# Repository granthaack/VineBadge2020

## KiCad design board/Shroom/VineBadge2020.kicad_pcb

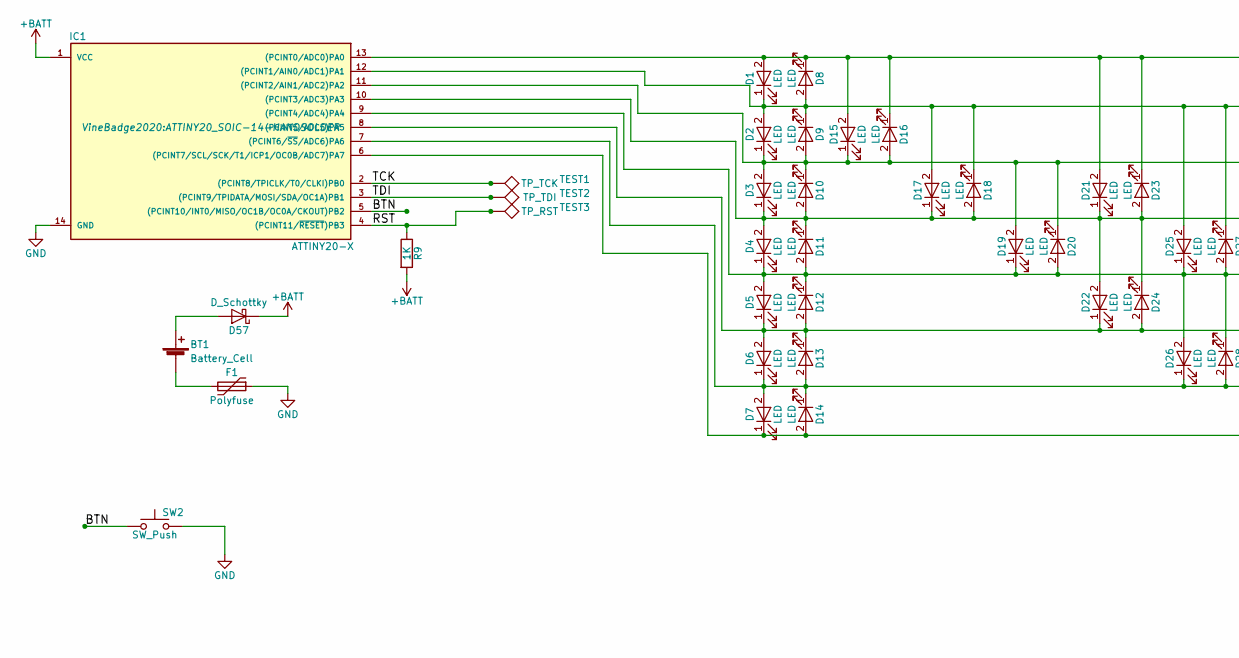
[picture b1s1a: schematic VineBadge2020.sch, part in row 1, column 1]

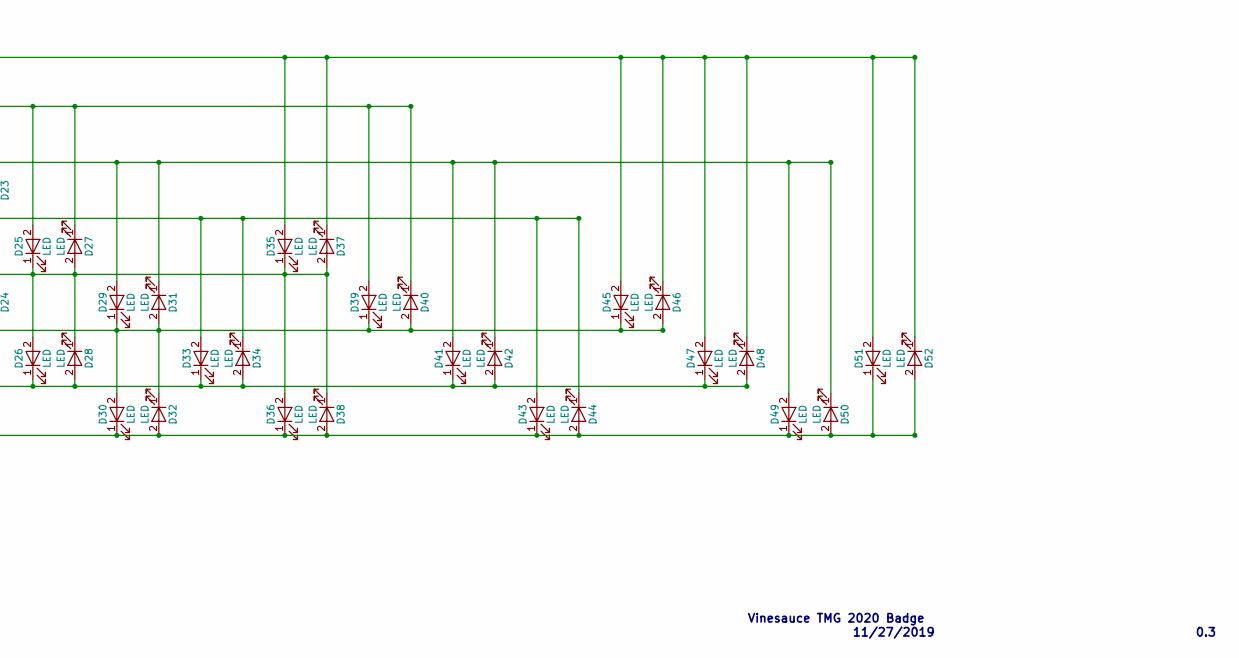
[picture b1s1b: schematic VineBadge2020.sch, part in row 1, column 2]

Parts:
BT1: Battery_Cell; COINCELL_20MM_HANDSOLDER
D1: LED; LED_0603; LCSC C205443
D2, D3, D4, D5, D6, D7, D8, D9, D10, D11, D12, D13, D14, D15, D16, D17, D18, D19, D20, D21, D22, D23, D24, D25, D26, D27, D28, D29, D30, D31, D32, D33, D34, D35, D36, D37, D38, D39, D40, D41, D42, D43, D44, D45, D46, D47, D48, D49, D50, D51, D52: LED; LED_0603
D57: D_Schottky; SOD-323_HandSoldering
F1: Polyfuse; R_0603_HandSoldering
IC1: ATTINY20-X; ATTINY20_SOIC-14-HANDSOLDER
R9: 1K; R_0805_HandSoldering
SW2: SW_Push; SW_SPST_TL3342
TEST1: TP_TCK; TestPoint_Pad_2.5x2.5mm
TEST2: TP_TDI; TestPoint_Pad_2.5x2.5mm
TEST3: TP_RST; TestPoint_Pad_2.5x2.5mm

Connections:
+BATT: D57.1 (K), IC1.1 (VCC), R9.2
/BTN: IC1.5 ((PCINT10/INT0/MISO/OC1B/OC0A/CKOUT)PB2), SW2.1
/RST: IC1.4 ((PCINT11/~RESET~)PB3), R9.1, TEST3.1
/TCK: IC1.2 ((PCINT8/TPICLK/T0/CLKI)PB0), TEST1.1
/TDI: IC1.3 ((PCINT9/TPIDATA/MOSI/SDA/OC1A)PB1), TEST2.1
GND: F1.1, IC1.14 (GND), SW2.2
unnamed: BT1.1 (+), D57.2 (A)
unnamed: BT1.2 (-), F1.2
unnamed: D1.1 (K), D2.2 (A), D8.2 (A), D9.1 (K), D17.2 (A), D18.1 (K), D25.2 (A), D27.1 (K), D39.2 (A), D40.1 (K), IC1.12 ((PCINT1/AIN0/ADC1)PA1)
unnamed: D1.2 (A), D8.1 (K), D15.2 (A), D16.1 (K), D21.2 (A), D23.1 (K), D35.2 (A), D37.1 (K), D45.2 (A), D46.1 (K), D47.2 (A), D48.1 (K), D51.2 (A), D52.1 (K), IC1.13 ((PCINT0/ADC0)PA0)
unnamed: D2.1 (K), D3.2 (A), D9.2 (A), D10.1 (K), D15.1 (K), D16.2 (A), D19.2 (A), D20.1 (K), D29.2 (A), D31.1 (K), D41.2 (A), D42.1 (K), D49.2 (A), D50.1 (K), IC1.11 ((PCINT2/AIN1/ADC2)PA2)
unnamed: D3.1 (K), D4.2 (A), D10.2 (A), D11.1 (K), D17.1 (K), D18.2 (A), D21.1 (K), D22.2 (A), D23.2 (A), D24.1 (K), D33.2 (A), D34.1 (K), D43.2 (A), D44.1 (K), IC1.10 ((PCINT3/ADC3)PA3)
unnamed: D4.1 (K), D5.2 (A), D11.2 (A), D12.1 (K), D19.1 (K), D20.2 (A), D25.1 (K), D26.2 (A), D27.2 (A), D28.1 (K), D35.1 (K), D36.2 (A), D37.2 (A), D38.1 (K), IC1.9 ((PCINT4/ADC4)PA4)
unnamed: D5.1 (K), D6.2 (A), D12.2 (A), D13.1 (K), D22.1 (K), D24.2 (A), D29.1 (K), D30.2 (A), D31.2 (A), D32.1 (K), D39.1 (K), D40.2 (A), D45.1 (K), D46.2 (A), IC1.8 ((PCINT5/ADC5)PA5)
unnamed: D6.1 (K), D7.2 (A), D13.2 (A), D14.1 (K), D26.1 (K), D28.2 (A), D33.1 (K), D34.2 (A), D41.1 (K), D42.2 (A), D47.1 (K), D48.2 (A), IC1.7 ((PCINT6/~SS~/ADC6)PA6)
unnamed: D7.1 (K), D14.2 (A), D30.1 (K), D32.2 (A), D36.1 (K), D38.2 (A), D43.1 (K), D44.2 (A), D49.1 (K), D50.2 (A), D51.1 (K), D52.2 (A), IC1.6 ((PCINT7/SCL/SCK/T1/ICP1/OC0B/ADC7)PA7)

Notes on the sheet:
Vinesauce TMG 2020 Badge
11/27/2019
0.3

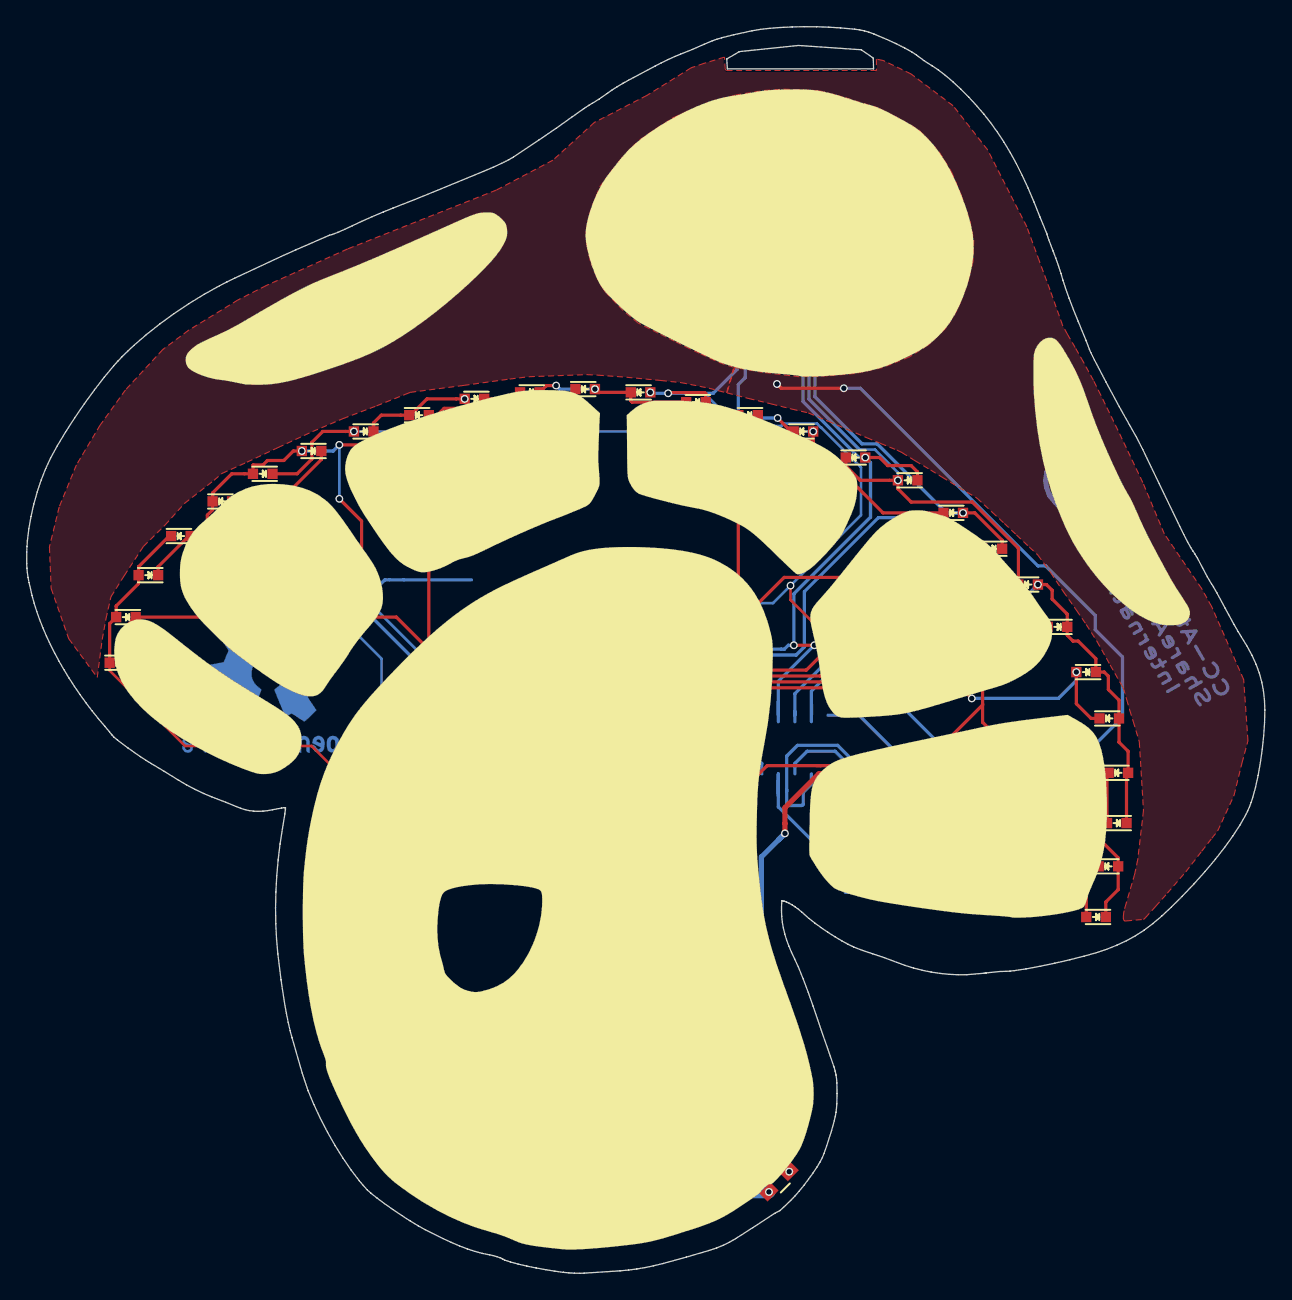
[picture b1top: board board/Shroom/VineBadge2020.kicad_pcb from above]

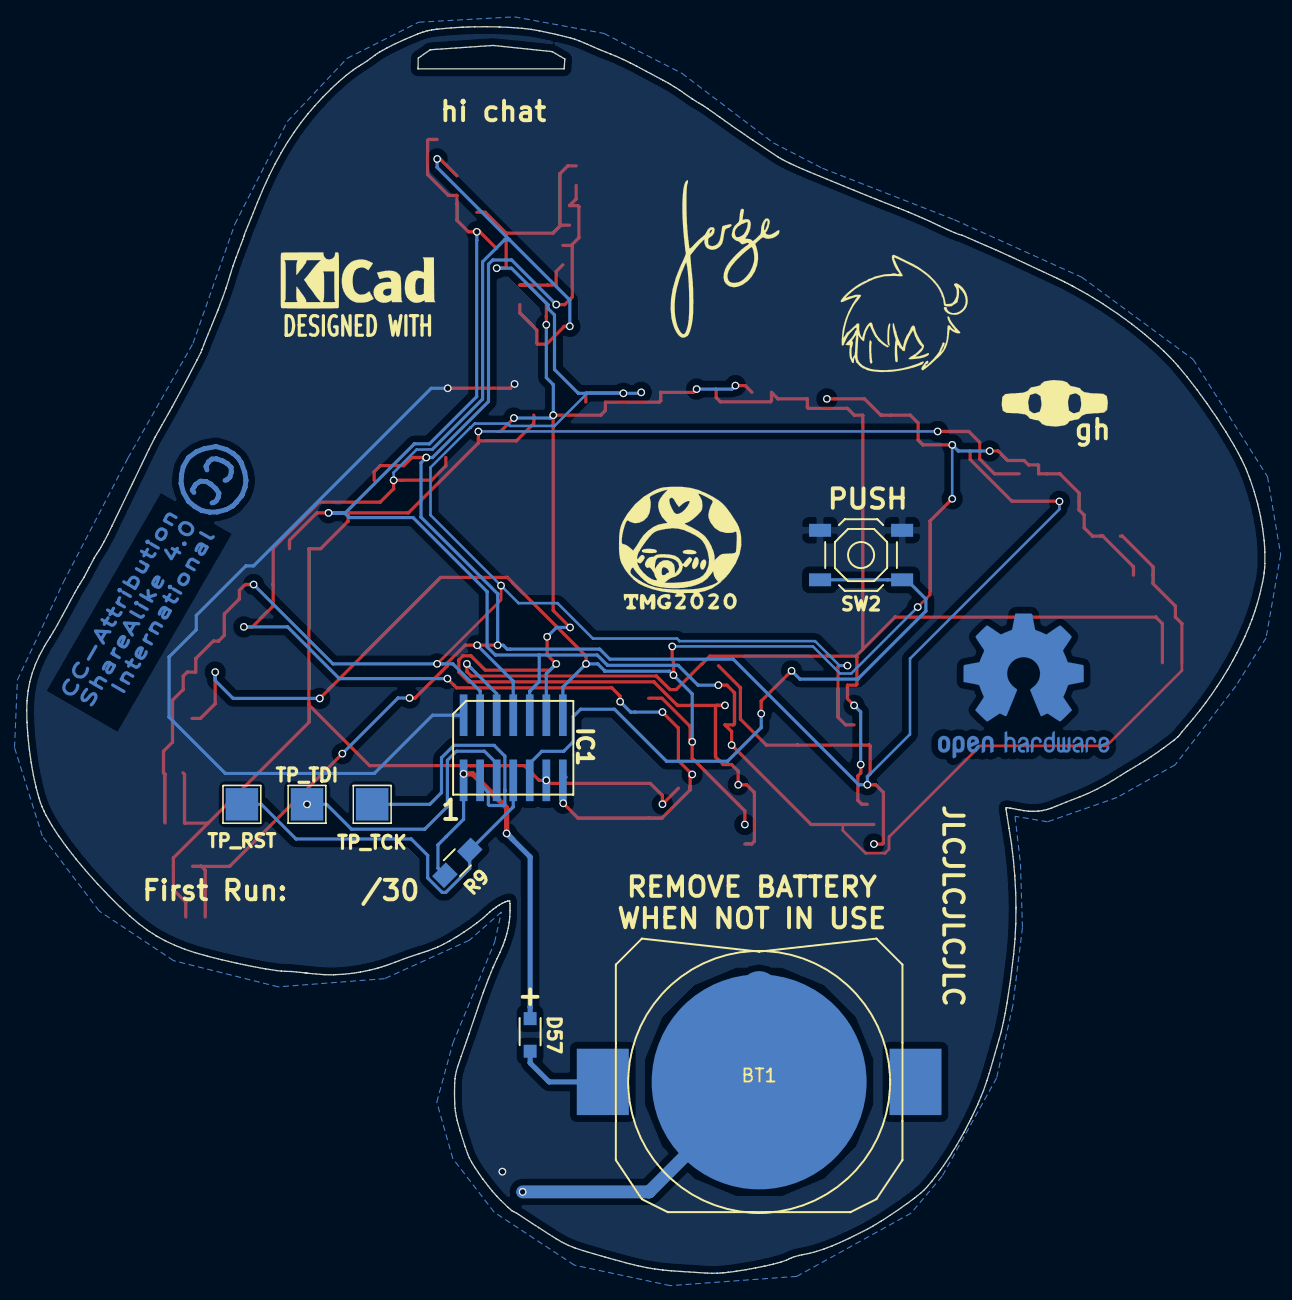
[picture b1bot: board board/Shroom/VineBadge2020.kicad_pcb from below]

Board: 2 copper layers, 95.0 x 95.7 mm, 61 parts (8 on the bottom side), 16 nets.

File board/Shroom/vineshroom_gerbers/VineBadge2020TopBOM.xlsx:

Comment | Designator | Footprint | LCSC Part #（optional）
LED_GREEN | D1 | 603 | C205443
LED_GREEN | D2 | 603 | C205443
LED_GREEN | D3 | 603 | C205443
LED_GREEN | D4 | 603 | C205443
LED_GREEN | D5 | 603 | C205443
LED_GREEN | D6 | 603 | C205443
LED_GREEN | D7 | 603 | C205443
LED_GREEN | D8 | 603 | C205443
LED_GREEN | D9 | 603 | C205443
LED_GREEN | D10 | 603 | C205443
LED_GREEN | D11 | 603 | C205443
LED_GREEN | D12 | 603 | C205443
LED_GREEN | D13 | 603 | C205443
LED_GREEN | D14 | 603 | C205443
LED_GREEN | D15 | 603 | C205443
LED_GREEN | D16 | 603 | C205443
LED_GREEN | D17 | 603 | C205443
LED_GREEN | D18 | 603 | C205443
LED_GREEN | D19 | 603 | C205443
LED_GREEN | D20 | 603 | C205443
LED_GREEN | D21 | 603 | C205443
LED_GREEN | D22 | 603 | C205443
LED_GREEN | D23 | 603 | C205443
LED_GREEN | D24 | 603 | C205443
LED_GREEN | D25 | 603 | C205443
LED_GREEN | D26 | 603 | C205443
LED_GREEN | D27 | 603 | C205443
LED_GREEN | D28 | 603 | C205443
LED_GREEN | D29 | 603 | C205443
LED_GREEN | D30 | 603 | C205443
LED_GREEN | D31 | 603 | C205443
LED_GREEN | D32 | 603 | C205443
LED_GREEN | D33 | 603 | C205443
LED_GREEN | D34 | 603 | C205443
LED_GREEN | D35 | 603 | C205443
LED_GREEN | D36 | 603 | C205443
LED_GREEN | D37 | 603 | C205443
LED_GREEN | D38 | 603 | C205443
LED_GREEN | D39 | 603 | C205443
LED_GREEN | D40 | 603 | C205443
LED_GREEN | D41 | 603 | C205443
LED_GREEN | D42 | 603 | C205443
LED_GREEN | D43 | 603 | C205443
LED_GREEN | D44 | 603 | C205443
LED_GREEN | D45 | 603 | C205443
LED_GREEN | D46 | 603 | C205443
LED_GREEN | D47 | 603 | C205443
LED_GREEN | D48 | 603 | C205443
LED_GREEN | D49 | 603 | C205443
LED_GREEN | D50 | 603 | C205443
LED_GREEN | D51 | 603 | C205443
LED_GREEN | D52 | 603 | C205443

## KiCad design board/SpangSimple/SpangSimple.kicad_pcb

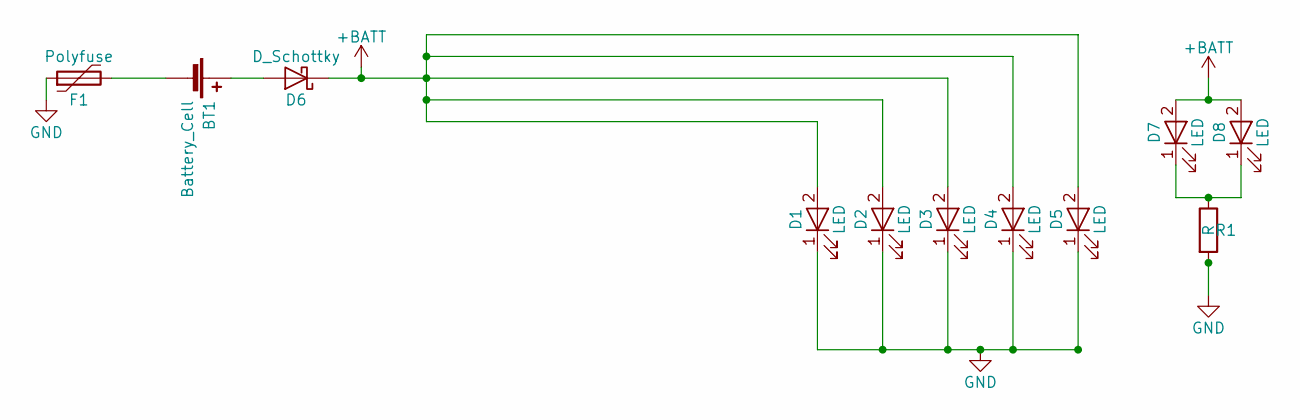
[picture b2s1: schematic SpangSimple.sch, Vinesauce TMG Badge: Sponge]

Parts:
BT1: Battery_Cell; COINCELL_20MM_HANDSOLDER
D1, D2, D3, D4, D5: LED; LED_0805_HandSoldering
D6: D_Schottky; SOD-323_HandSoldering
D7, D8: LED; LED_0603_Handsoldering
F1: Polyfuse; R_0603_HandSoldering
R1: R; R_0805_HandSoldering

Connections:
+BATT: D1.2 (A), D2.2 (A), D3.2 (A), D4.2 (A), D5.2 (A), D6.1 (K), D7.2 (A), D8.2 (A)
GND: D1.1 (K), D2.1 (K), D3.1 (K), D4.1 (K), D5.1 (K), F1.1, R1.2
unnamed: BT1.1 (+), D6.2 (A)
unnamed: BT1.2 (-), F1.2
unnamed: D7.1 (K), D8.1 (K), R1.1

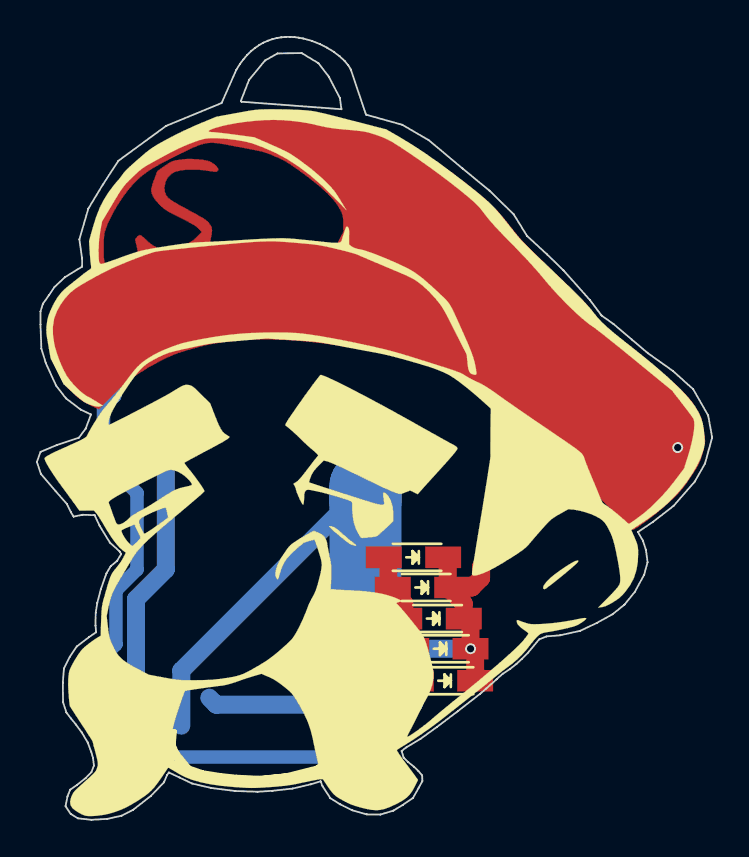
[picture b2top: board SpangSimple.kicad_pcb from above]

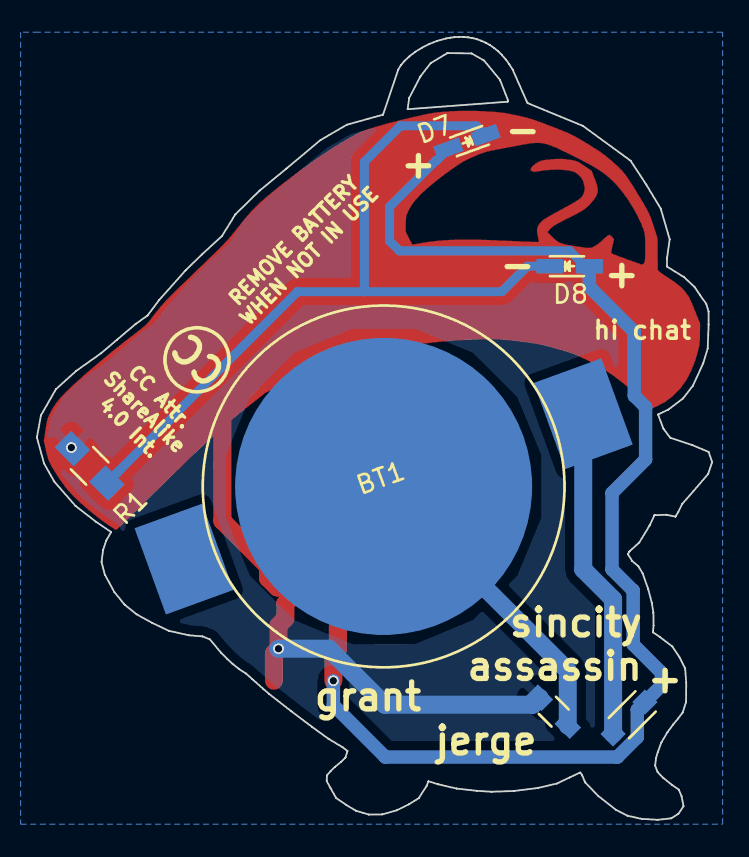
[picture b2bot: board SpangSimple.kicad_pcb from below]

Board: 2 copper layers, 37.5 x 43.5 mm, 11 parts (6 on the bottom side), 5 nets.

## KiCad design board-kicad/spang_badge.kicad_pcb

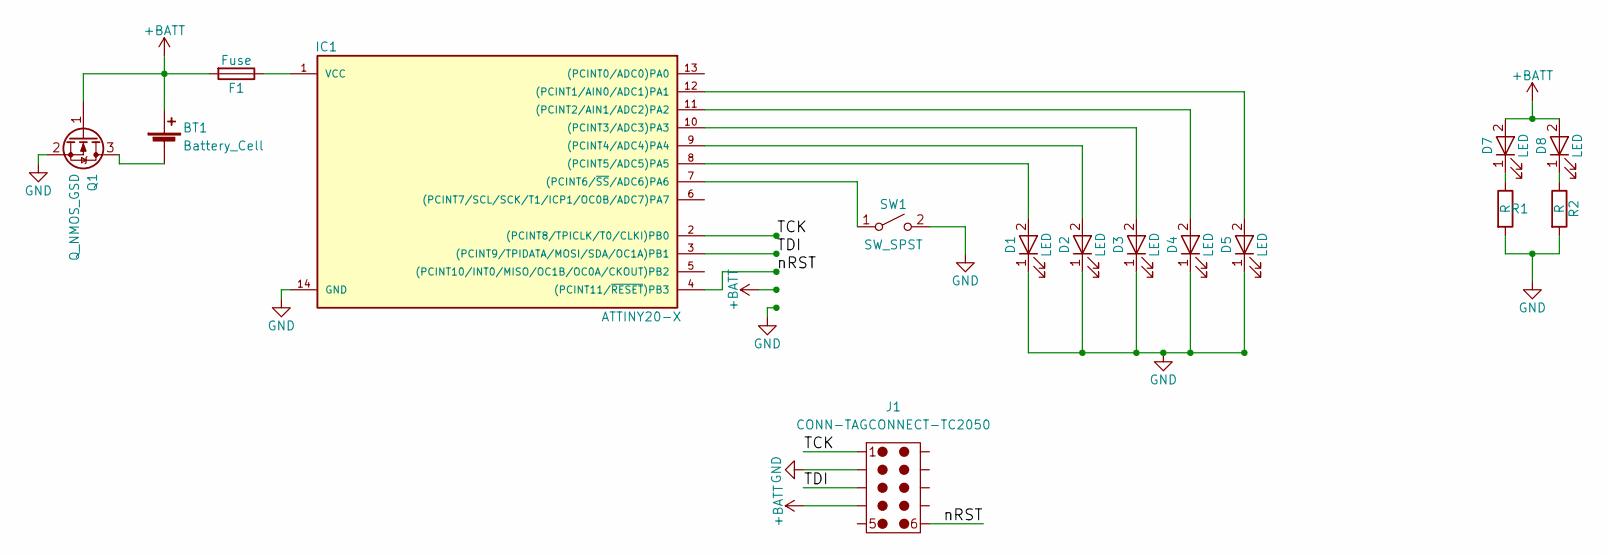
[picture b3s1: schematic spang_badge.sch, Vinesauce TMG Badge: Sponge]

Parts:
BT1: Battery_Cell; COINCELL_20MM
D1, D2, D3, D4, D5, D7, D8: LED; LED_0603
F1: Fuse; Fuse_SMD1206_HandSoldering
IC1: ATTINY20-X; ATTINY20_SOIC-14
J1: CONN-TAGCONNECT-TC2050; TC2050-All_Holes
Q1: Q_NMOS_GSD; SOT-23
R1, R2: R; R_0603_HandSoldering
SW1: SW_SPST; EVQ-P7B01P

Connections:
+BATT: BT1.1 (+), D7.2 (A), D8.2 (A), F1.2, J1.4, Q1.1 (G)
/TCK: IC1.2 ((PCINT8/TPICLK/T0/CLKI)PB0), J1.1
/TDI: IC1.3 ((PCINT9/TPIDATA/MOSI/SDA/OC1A)PB1), J1.3
/nRST: IC1.4 ((PCINT11/~RESET~)PB3), J1.6
GND: D1.1 (K), D2.1 (K), D3.1 (K), D4.1 (K), D5.1 (K), IC1.14 (GND), J1.2, Q1.2 (S), R1.2, R2.2, SW1.2 (B)
unnamed: BT1.2 (-), Q1.3 (D)
unnamed: D1.2 (A), IC1.8 ((PCINT5/ADC5)PA5)
unnamed: D2.2 (A), IC1.9 ((PCINT4/ADC4)PA4)
unnamed: D3.2 (A), IC1.10 ((PCINT3/ADC3)PA3)
unnamed: D4.2 (A), IC1.11 ((PCINT2/AIN1/ADC2)PA2)
unnamed: D5.2 (A), IC1.12 ((PCINT1/AIN0/ADC1)PA1)
unnamed: D7.1 (K), R1.1
unnamed: D8.1 (K), R2.1
unnamed: F1.1, IC1.1 (VCC)
unnamed: IC1.7 ((PCINT6/~SS~/ADC6)PA6), SW1.1 (A)

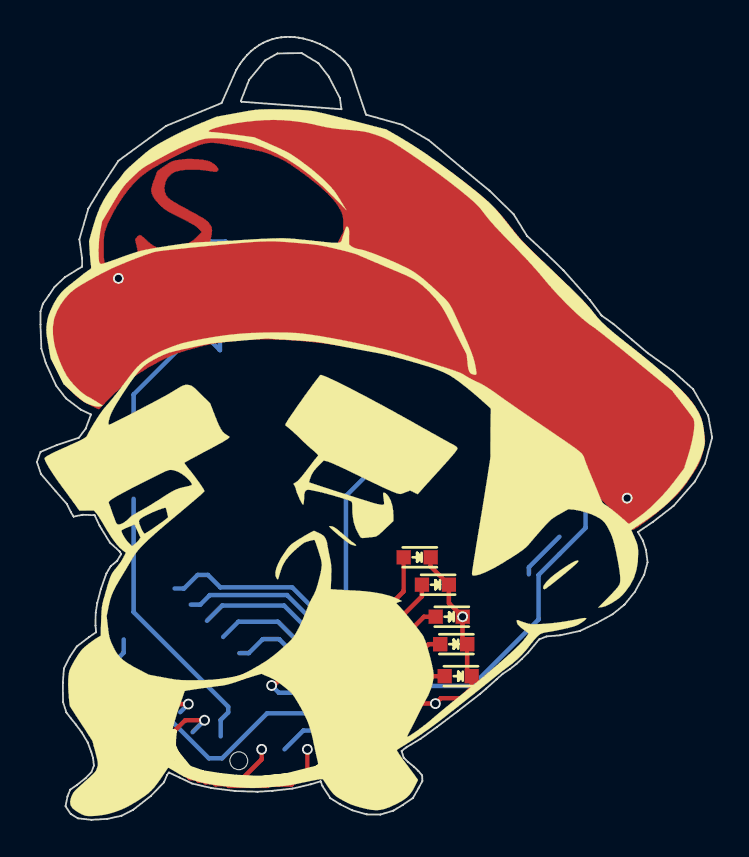
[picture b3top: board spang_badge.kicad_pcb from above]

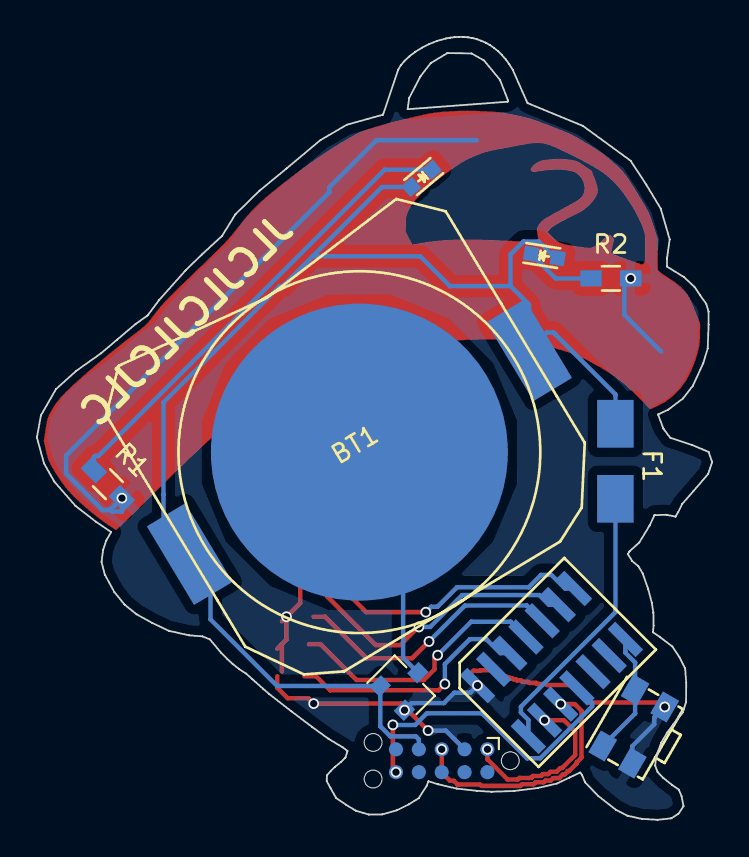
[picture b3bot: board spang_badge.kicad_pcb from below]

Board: 2 copper layers, 37.5 x 43.5 mm, 15 parts (10 on the bottom side), 15 nets.

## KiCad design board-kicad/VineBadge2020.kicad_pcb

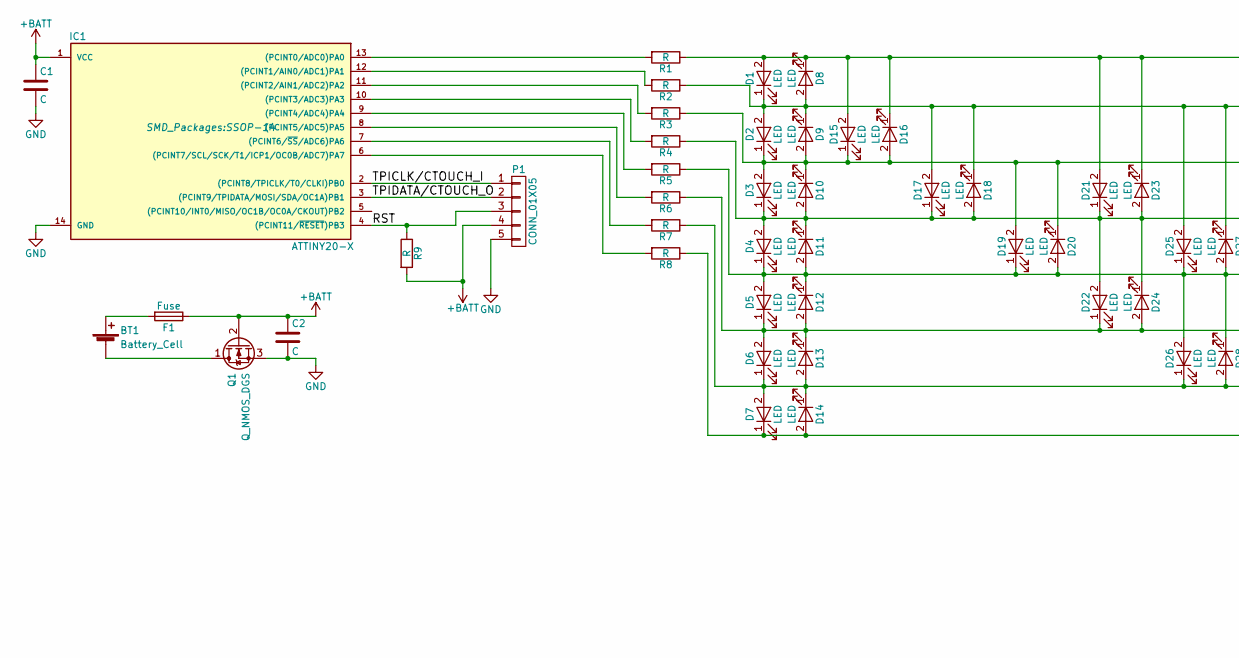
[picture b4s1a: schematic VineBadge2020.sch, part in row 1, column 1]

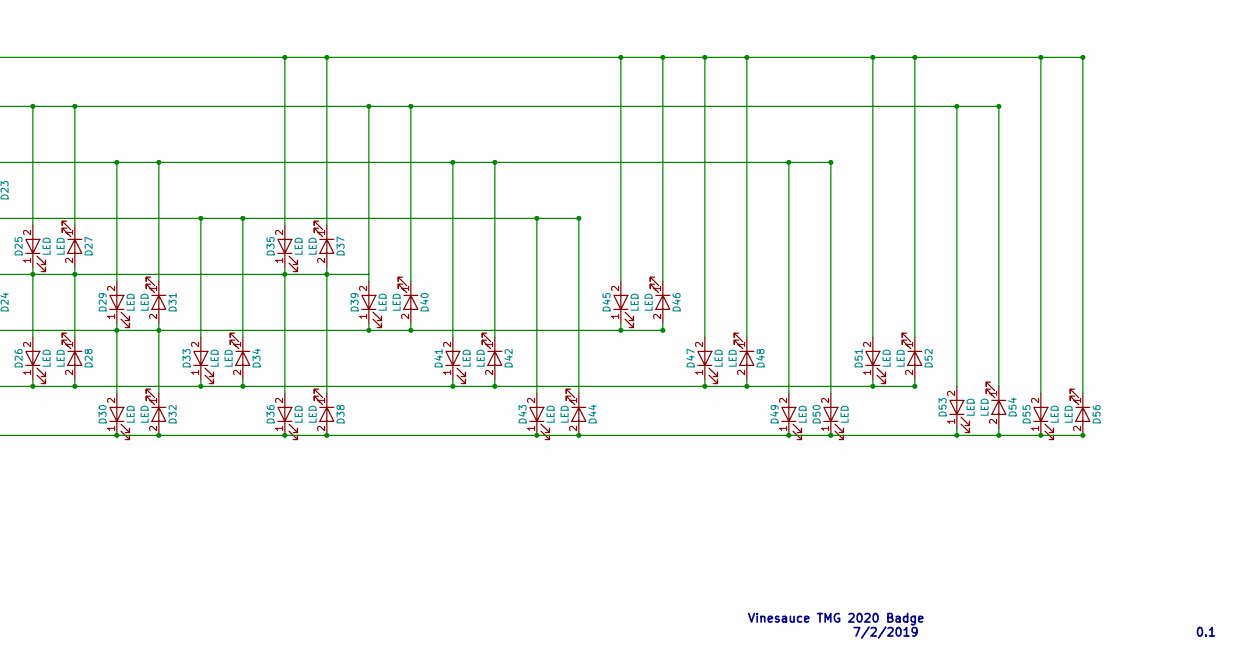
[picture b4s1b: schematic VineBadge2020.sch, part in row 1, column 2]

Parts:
BT1: Battery_Cell
C1, C2: C; C_0603
D1, D2, D3, D4, D5, D6, D7, D8, D9, D10, D11, D12, D13, D14, D15, D16, D17, D18, D19, D20, D21, D22, D23, D24, D25, D26, D27, D28, D29, D30, D31, D32, D33, D34, D35, D36, D37, D38, D39, D40, D41, D42, D43, D44, D45, D46, D47, D48, D49, D50, D51, D52, D53, D54, D55, D56: LED; LED_0603
F1: Fuse; Fuse_SMD1206_Reflow
IC1: ATTINY20-X; SSOP-14
P1: CONN_01X05; Pin_Header_Straight_1x05
Q1: Q_NMOS_DGS; SOT-23
R1, R2, R3, R4, R5, R6, R7, R8, R9: R; R_0805

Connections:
+BATT: C1.1, C2.1, F1.1, IC1.1 (VCC), P1.4, Q1.2 (G), R9.2
/RST: IC1.4 ((PCINT11/~RESET~)PB3), P1.3, R9.1
/TPICLK/CTOUCH_I: IC1.2 ((PCINT8/TPICLK/T0/CLKI)PB0), P1.1
/TPIDATA/CTOUCH_O: IC1.3 ((PCINT9/TPIDATA/MOSI/SDA/OC1A)PB1), P1.2
GND: C1.2, C2.2, IC1.14 (GND), P1.5, Q1.3 (S)
unnamed: BT1.1 (+), F1.2
unnamed: BT1.2 (-), Q1.1 (D)
unnamed: D1.1 (K), D2.2 (A), D8.2 (A), D9.1 (K), D17.2 (A), D18.1 (K), D25.2 (A), D27.1 (K), D39.2 (A), D40.1 (K), D53.2 (A), D54.1 (K), R2.1
unnamed: D1.2 (A), D8.1 (K), D15.2 (A), D16.1 (K), D21.2 (A), D23.1 (K), D35.2 (A), D37.1 (K), D45.2 (A), D46.1 (K), D47.2 (A), D48.1 (K), D51.2 (A), D52.1 (K), D55.2 (A), D56.1 (K), R1.1
unnamed: D2.1 (K), D3.2 (A), D9.2 (A), D10.1 (K), D15.1 (K), D16.2 (A), D19.2 (A), D20.1 (K), D29.2 (A), D31.1 (K), D41.2 (A), D42.1 (K), D49.2 (A), D50.2 (A), R3.1
unnamed: D3.1 (K), D4.2 (A), D10.2 (A), D11.1 (K), D17.1 (K), D18.2 (A), D21.1 (K), D22.2 (A), D23.2 (A), D24.1 (K), D33.2 (A), D34.1 (K), D43.2 (A), D44.1 (K), R4.1
unnamed: D4.1 (K), D5.2 (A), D11.2 (A), D12.1 (K), D19.1 (K), D20.2 (A), D25.1 (K), D26.2 (A), D27.2 (A), D28.1 (K), D35.1 (K), D36.2 (A), D37.2 (A), D38.1 (K), R5.1
unnamed: D5.1 (K), D6.2 (A), D12.2 (A), D13.1 (K), D22.1 (K), D24.2 (A), D29.1 (K), D30.2 (A), D31.2 (A), D32.1 (K), D39.1 (K), D40.2 (A), D45.1 (K), D46.2 (A), R6.1
unnamed: D6.1 (K), D7.2 (A), D13.2 (A), D14.1 (K), D26.1 (K), D28.2 (A), D33.1 (K), D34.2 (A), D41.1 (K), D42.2 (A), D47.1 (K), D48.2 (A), D51.1 (K), D52.2 (A), R7.1
unnamed: D7.1 (K), D14.2 (A), D30.1 (K), D32.2 (A), D36.1 (K), D38.2 (A), D43.1 (K), D44.2 (A), D49.1 (K), D50.1 (K), D53.1 (K), D54.2 (A), D55.1 (K), D56.2 (A), R8.1
unnamed: IC1.6 ((PCINT7/SCL/SCK/T1/ICP1/OC0B/ADC7)PA7), R8.2
unnamed: IC1.7 ((PCINT6/~SS~/ADC6)PA6), R7.2
unnamed: IC1.8 ((PCINT5/ADC5)PA5), R6.2
unnamed: IC1.9 ((PCINT4/ADC4)PA4), R5.2
unnamed: IC1.10 ((PCINT3/ADC3)PA3), R4.2
unnamed: IC1.11 ((PCINT2/AIN1/ADC2)PA2), R3.2
unnamed: IC1.12 ((PCINT1/AIN0/ADC1)PA1), R2.2
unnamed: IC1.13 ((PCINT0/ADC0)PA0), R1.2

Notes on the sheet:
Vinesauce TMG 2020 Badge
7/2/2019
0.1

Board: 2 copper layers, 71 parts (0 on the bottom side), 21 nets, no tracks yet.

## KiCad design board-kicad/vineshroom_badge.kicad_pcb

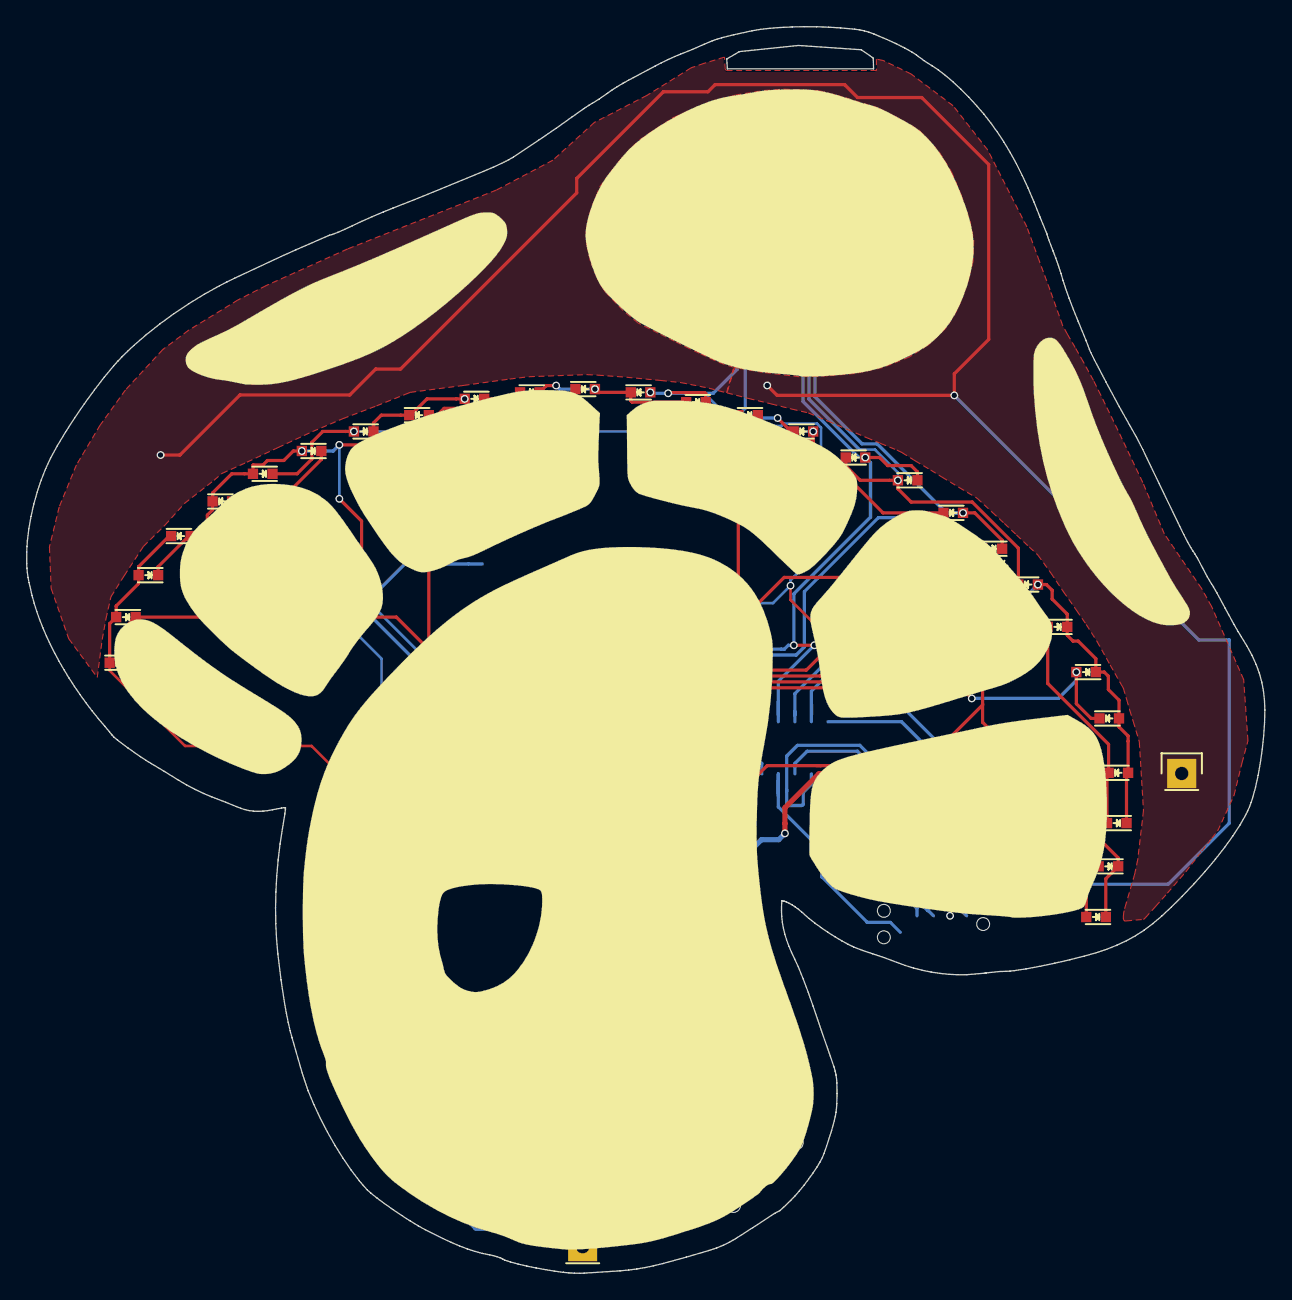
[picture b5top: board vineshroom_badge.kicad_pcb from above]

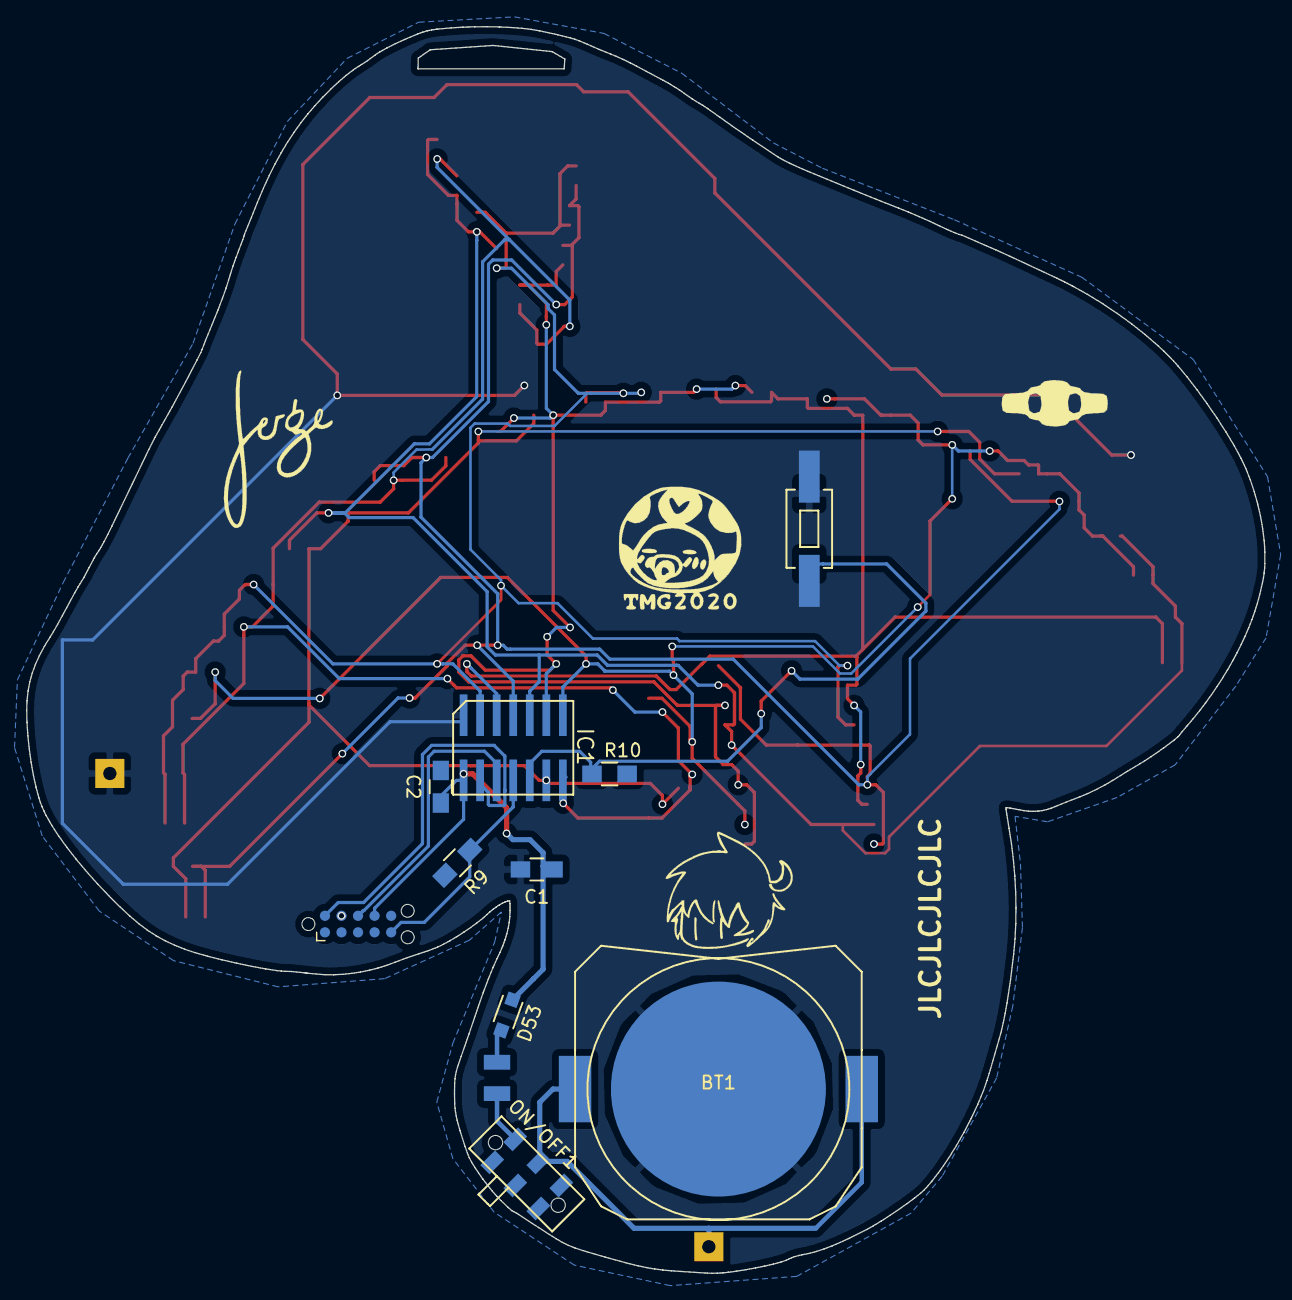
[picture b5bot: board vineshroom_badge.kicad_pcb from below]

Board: 2 copper layers, 95.0 x 95.7 mm, 65 parts (11 on the bottom side), 17 nets.

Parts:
BT1: Battery_Cell; COINCELL_20MM
C1: 100nF; C_0805_HandSoldering
C2: 1uF; C_0805_HandSoldering
D1, D2, D3, D4, D5, D6, D7, D8, D9, D10, D11, D12, D13, D14, D15, D16, D17, D18, D19, D20, D21, D22, D23, D24, D25, D26, D27, D28, D29, D30, D31, D32, D33, D34, D35, D36, D37, D38, D39, D40, D41, D42, D43, D44, D45, D46, D47, D48, D49, D50, D51, D52: LED; LED_0603
D53: D_Schottky; SOD-323_HandSoldering
F1: Fuse; Fuse_SMD1206_Reflow
IC1: ATTINY20-X; ATTINY20_SOIC-14-HANDSOLDER
J1: CONN-TAGCONNECT-TC2050; TC2050-All_Holes
ON/OFF1: SW_DPDT_x2; JS202011JAQN
R9, R10: 1K; R_0805_HandSoldering
SW1: SW_SPST; SW_SPST_EVQPE1
TP_BATT1: TEST; Pin_Header_Straight_1x01
TP_GND1: TEST; Pin_Header_Straight_1x01

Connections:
+BATT: C1.1, C2.1, D53.1, IC1.1, J1.7, R9.2, R10.2
/BTN: IC1.5, R10.1, SW1.1
/RST: IC1.4, J1.5, R9.1
/TCK: IC1.2, J1.10
/TDI: IC1.3, J1.8
GND: BT1.2, C1.2, C2.2, IC1.14, J1.9, SW1.2, TP_GND1.1
unnamed: BT1.1, ON/OFF1.2, TP_BATT1.1
unnamed: D1.1, D2.2, D8.2, D9.1, D17.2, D18.1, D25.2, D27.1, D39.2, D40.1, IC1.12
unnamed: D1.2, D8.1, D15.2, D16.1, D21.2, D23.1, D35.2, D37.1, D45.2, D46.1, D47.2, D48.1, D51.2, D52.1, IC1.13
unnamed: D2.1, D3.2, D9.2, D10.1, D15.1, D16.2, D19.2, D20.1, D29.2, D31.1, D41.2, D42.1, D49.2, D50.2, IC1.11
unnamed: D3.1, D4.2, D10.2, D11.1, D17.1, D18.2, D21.1, D22.2, D23.2, D24.1, D33.2, D34.1, D43.2, D44.1, IC1.10
unnamed: D4.1, D5.2, D11.2, D12.1, D19.1, D20.2, D25.1, D26.2, D27.2, D28.1, D35.1, D36.2, D37.2, D38.1, IC1.9
unnamed: D5.1, D6.2, D12.2, D13.1, D22.1, D24.2, D29.1, D30.2, D31.2, D32.1, D39.1, D40.2, D45.1, D46.2, IC1.8
unnamed: D6.1, D7.2, D13.2, D14.1, D26.1, D28.2, D33.1, D34.2, D41.1, D42.2, D47.1, D48.2, D51.1, D52.2, IC1.7
unnamed: D7.1, D14.2, D30.1, D32.2, D36.1, D38.2, D43.1, D44.2, D49.1, D50.1, IC1.6
unnamed: D53.2, F1.1
unnamed: F1.2, ON/OFF1.1

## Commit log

2019-07-03 made directory for CAD
2019-07-04 switched to KiCAD because I'm a FOSS loser
2019-07-08 tracing vineshroom graphics for board
2019-07-31 guess I forgot to commit
2019-08-16 made schematic and art for the sponge badge
2019-08-17 fixed the Shroom design so the mouth isn't covered by silkscreen
2019-08-18 cleaned up sponge
2019-08-19 ordered some parts to experiment
2019-08-22 starting LED placement
2019-08-23 routing sponge. Need to figure out how to rename polygons to GND
2019-08-23 need to run DRC
2019-08-26 final touches on shroom badge
2019-09-13 working on spang badge v2. TODO: fix B-CU
2019-09-24 workin on cryptid shroom
2019-11-26 fixed pinout on programming header, some other shit too whatever lets get this done
2019-11-27 finally cleaned up files
2019-11-27 cleaned up spang simple
2019-11-27 cleaned up file structure
2019-12-08 sending off gerbers
2019-12-09 added a list of LED settings
2019-12-09 created a progmem led map, need ot test
2019-12-13 removed unecessary fuse, repositioned things on board
2020-01-06 removed programming stuff, getting ready for final revision. Just needs last checks
2020-02-15 kfdjkd
